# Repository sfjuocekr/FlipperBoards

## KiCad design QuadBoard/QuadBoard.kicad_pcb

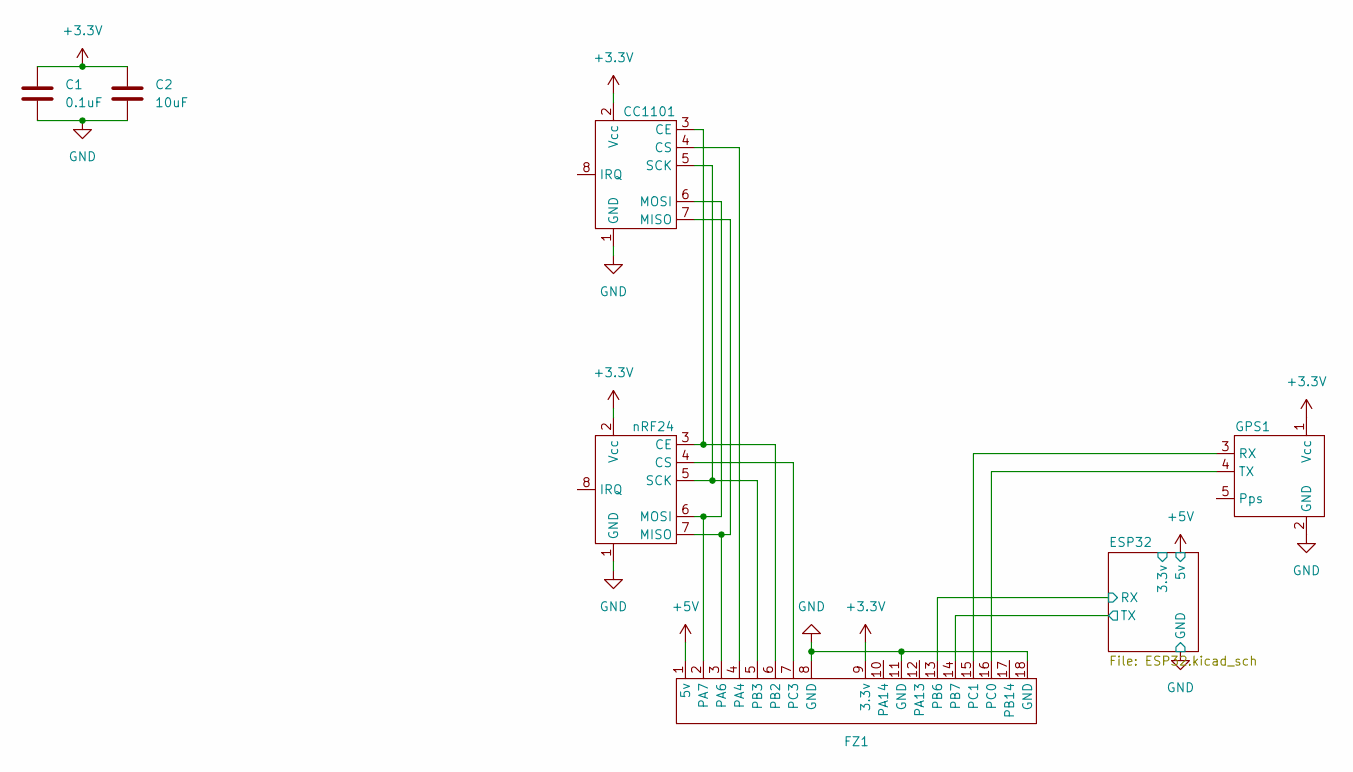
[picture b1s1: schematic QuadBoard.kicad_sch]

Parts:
C1: 0.1uF; C_Disc_D6.0mm_W2.5mm_P5.00mm
C2: 10uF; C_Radial_D4.0mm_H7.0mm_P1.50mm
CC1101: C1101
FZ1: FZ
GPS1: GPS
nRF24: nRF24

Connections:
+3.3V: C1.1, C2.1, CC1101.2 (Vcc), FZ1.9 (3.3v), GPS1.1 (Vcc), nRF24.2 (Vcc)
+5V: FZ1.1 (5v); also elsewhere on the board
/ESP32/RX: FZ1.13 (PB6); also elsewhere on the board
/ESP32/TX: FZ1.14 (PB7); also elsewhere on the board
GND: C1.2, C2.2, CC1101.1 (GND), FZ1.8 (GND), FZ1.11 (GND), FZ1.18 (GND), GPS1.2 (GND), nRF24.1 (GND); also elsewhere on the board
unnamed: CC1101.3 (CE), FZ1.6 (PB2), nRF24.3 (CE)
unnamed: CC1101.4 (CS), FZ1.4 (PA4)
unnamed: CC1101.7 (MISO), FZ1.3 (PA6), nRF24.7 (MISO)
unnamed: CC1101.6 (MOSI), FZ1.2 (PA7), nRF24.6 (MOSI)
unnamed: CC1101.5 (SCK), FZ1.5 (PB3), nRF24.5 (SCK)
unnamed: FZ1.16 (PC0), GPS1.4 (TX)
unnamed: FZ1.15 (PC1), GPS1.3 (RX)
unnamed: FZ1.7 (PC3), nRF24.4 (CS)

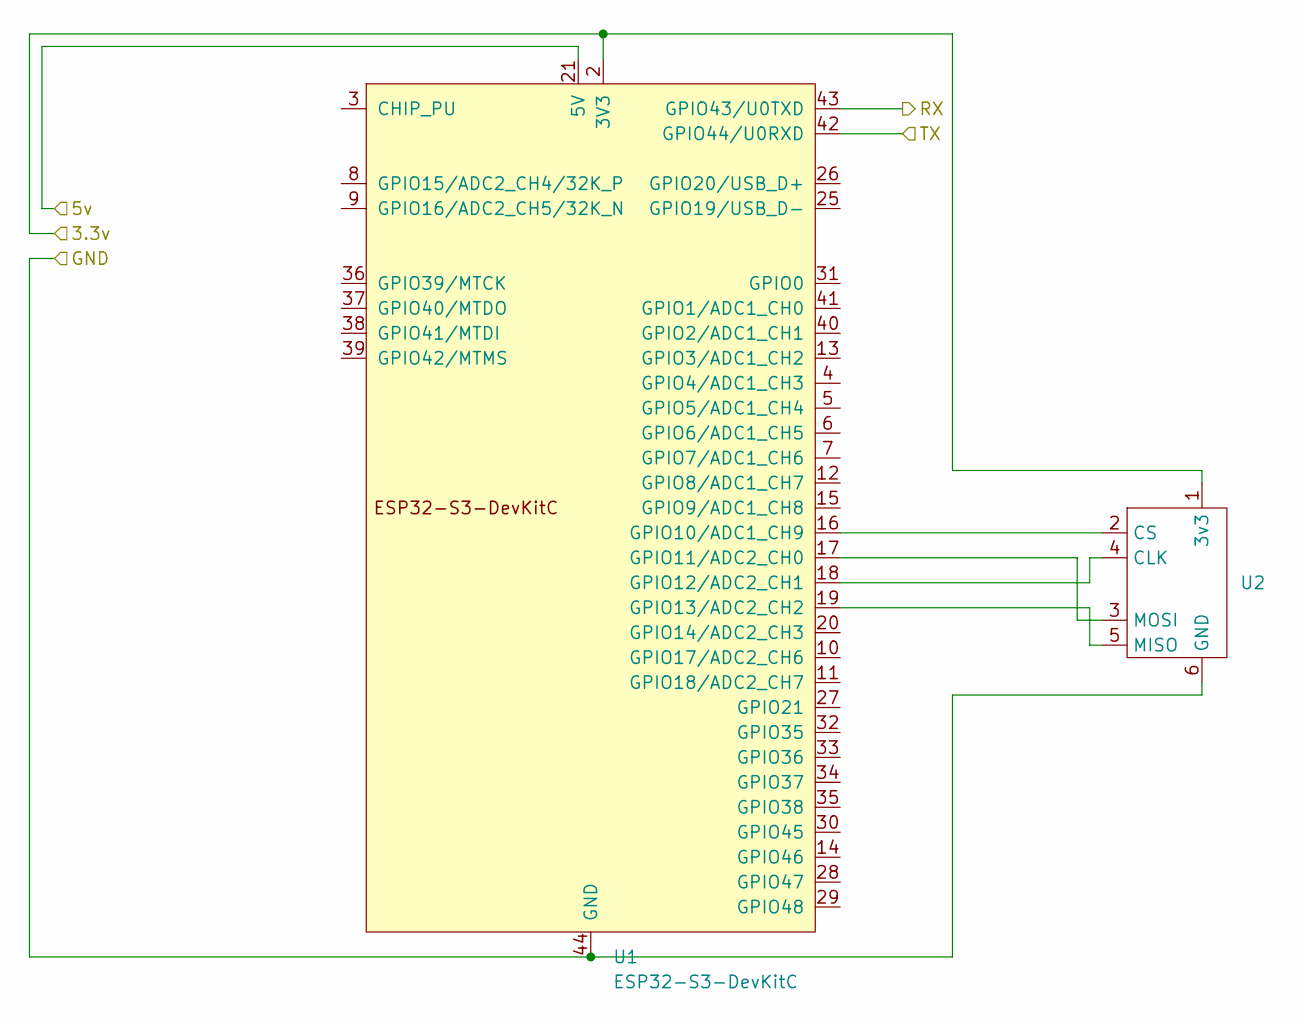
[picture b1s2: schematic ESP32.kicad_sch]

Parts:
U1: ESP32-S3-DevKitC
U2: SD

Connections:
+5V: U1.21 (5V); also elsewhere on the board
/ESP32/3.3v: U1.1 (3V3), U1.2 (3V3), U2.1 (3v3)
/ESP32/RX: U1.43 (GPIO43/U0TXD); also elsewhere on the board
/ESP32/TX: U1.42 (GPIO44/U0RXD); also elsewhere on the board
GND: U1.22 (GND), U1.23 (GND), U1.24 (GND), U1.44 (GND), U2.6 (GND); also elsewhere on the board
unnamed: U1.16 (GPIO10/ADC1_CH9), U2.2 (CS)
unnamed: U1.17 (GPIO11/ADC2_CH0), U2.3 (MOSI)
unnamed: U1.18 (GPIO12/ADC2_CH1), U2.4 (CLK)
unnamed: U1.19 (GPIO13/ADC2_CH2), U2.5 (MISO)

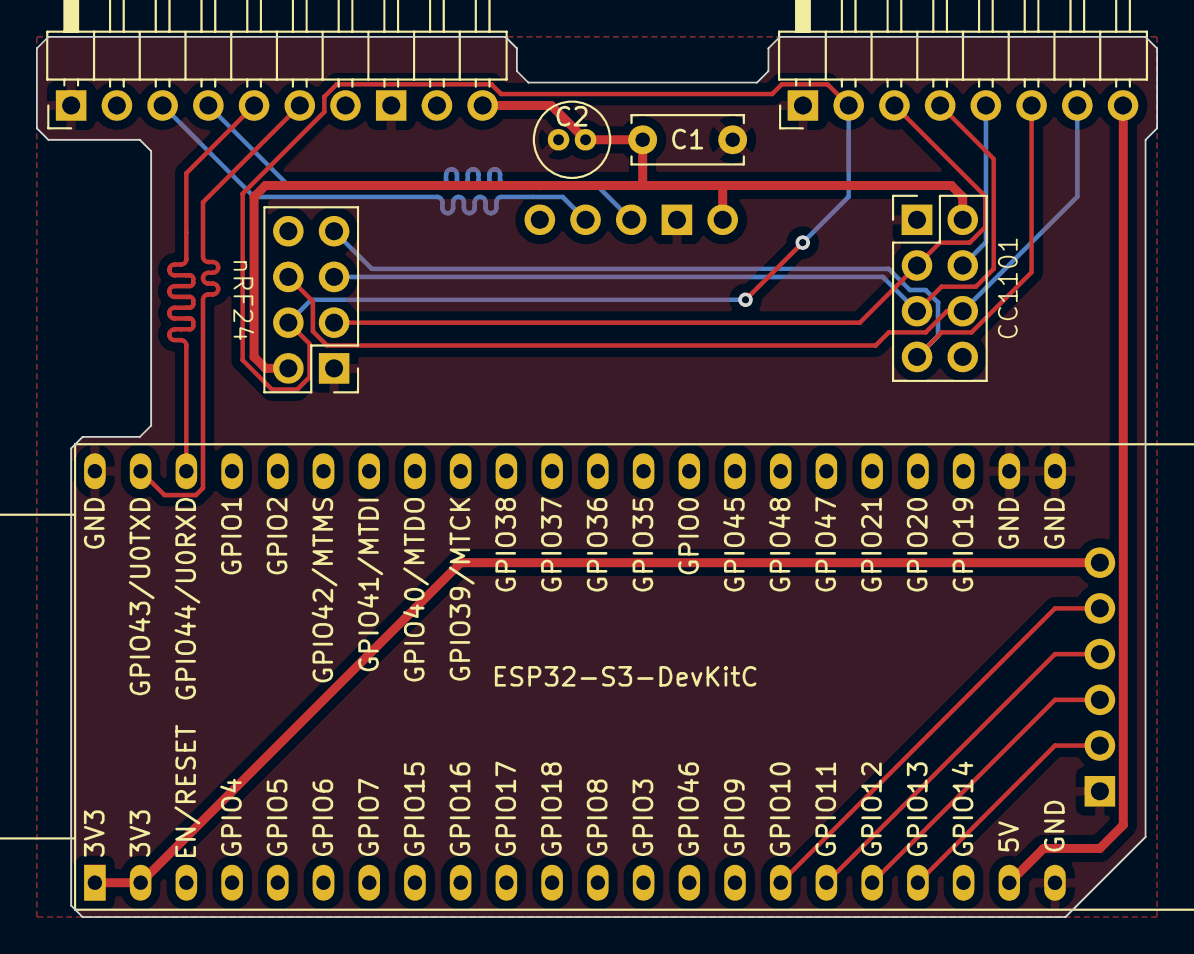
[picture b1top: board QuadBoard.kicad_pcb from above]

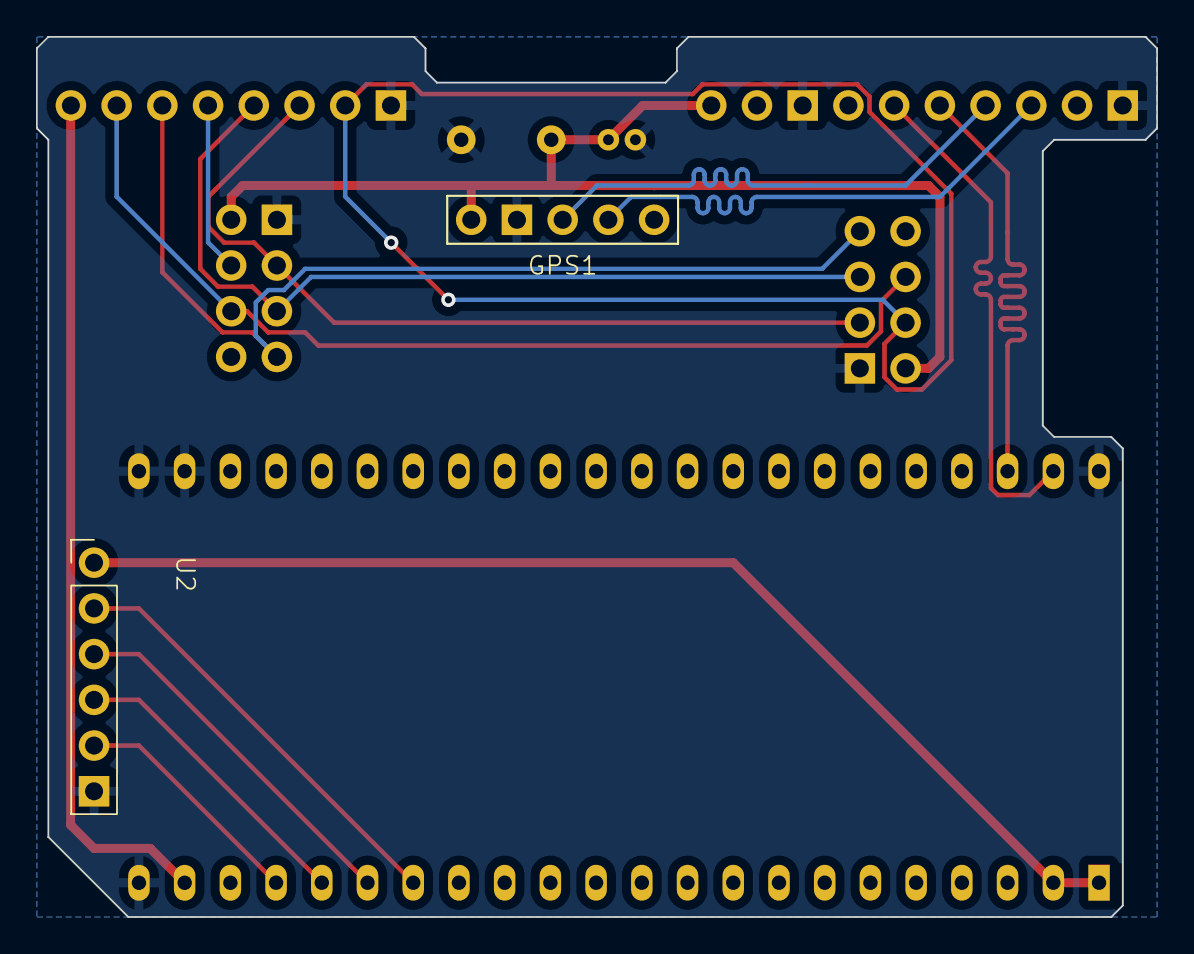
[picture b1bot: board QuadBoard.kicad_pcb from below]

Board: 2 copper layers, 62.2 x 48.9 mm, 8 parts (2 on the bottom side), 18 nets.

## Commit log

2023-12-30 Update SD footprint
2023-12-30 Update footprints
